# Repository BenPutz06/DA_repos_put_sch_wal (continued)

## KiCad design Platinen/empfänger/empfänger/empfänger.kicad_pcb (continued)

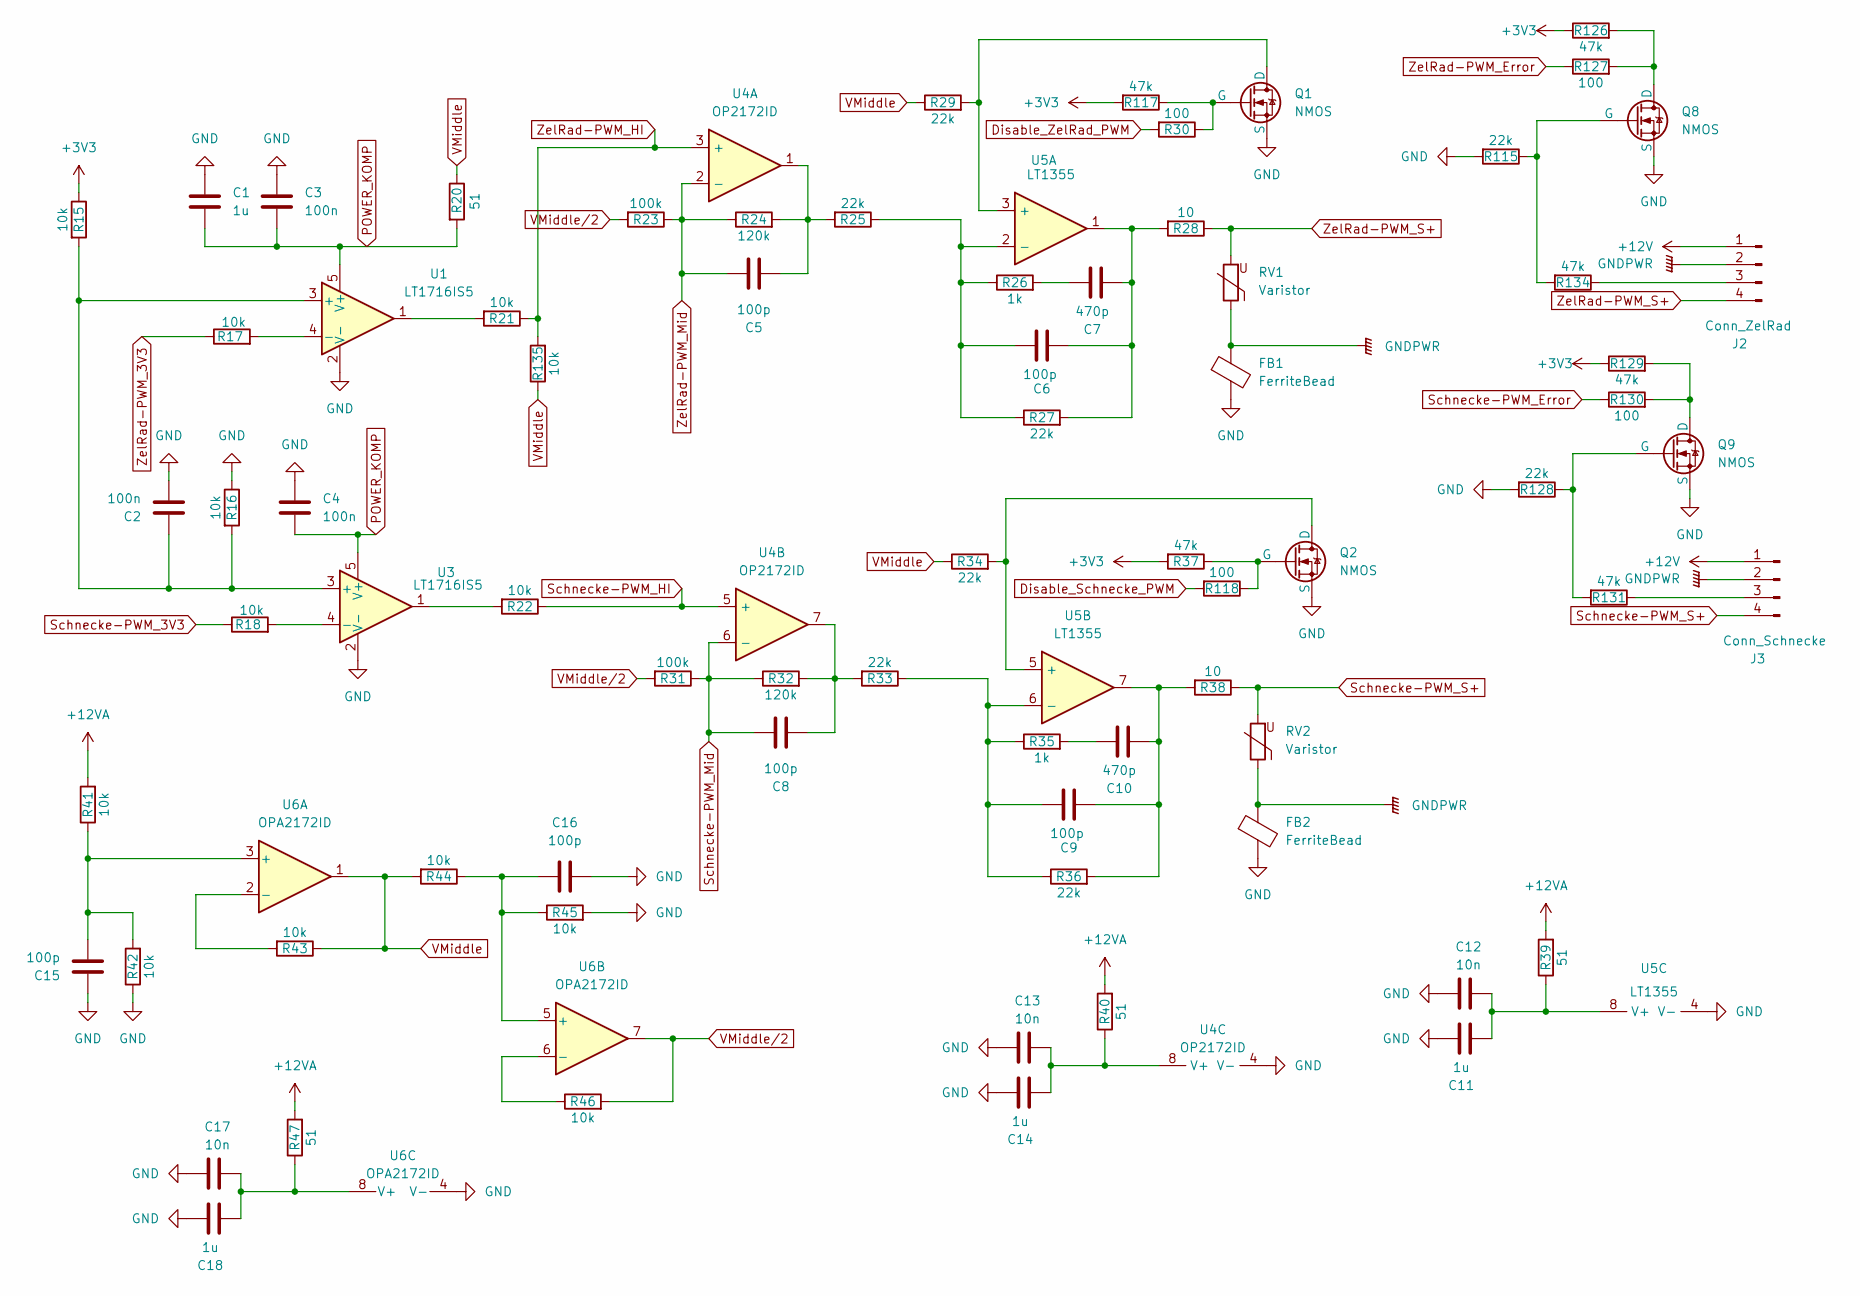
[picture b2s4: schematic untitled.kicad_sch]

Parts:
C1, C11, C14, C18: 1u; C_1206_3216Metric; Part-NO C1206C105K4RAC
C2, C3, C4: 100n; C_0805_2012Metric; Part-NO CC0805KRX7R9BB104
C5, C6, C8, C9, C15, C16: 100p; C_0805_2012Metric; Part-NO C0805C101J5GACTU
C7, C10: 470p; C_0805_2012Metric
C12, C13, C17: 10n; C_0603_1608Metric; Part-NO CC0603KRX7R9BB103
FB1, FB2: FerriteBead; R_1206_3216Metric; Part-NO WE-CBF_74279218
J2: Conn_ZelRad; PhoenixContact_MSTBVA_2,5_4-G-5,08_1x04_P5.08mm_Vertical; Part-NO MSTBV2_5/4-G-5_08
J3: Conn_Schnecke; PhoenixContact_MSTBVA_2,5_4-G-5,08_1x04_P5.08mm_Vertical; Part-NO MSTBV2_5/4-G-5_08
Q1, Q2, Q8, Q9: NMOS; TSOT-23; Part-NO FDV305N
R15, R16, R17, R18, R21, R22, R41, R42, R43, R44, R45, R46, R135: 10k; R_0603_1608Metric; Part-NO CRG0603F10K
R20, R39, R40, R47: 51; R_1206_3216Metric; Part-NO CRG1206F51R
R23, R31: 100k; R_0603_1608Metric; Part-NO CRG0603F100K
R24, R32: 120k; R_0603_1608Metric; Part-NO CRG0603F120K
R25, R27, R29, R33, R34, R36, R115, R128: 22k; R_0603_1608Metric; Part-NO CRG0603F22K
R26, R35: 1k; R_0603_1608Metric; Part-NO CRG0603F1K0
R28, R38: 10; R_1206_3216Metric
R30, R118, R127, R130: 100; R_0603_1608Metric
R37, R117, R126, R129: 47k; R_0603_1608Metric; Part-NO CRG0603F47K
R131, R134: 47k; R_0603_1608Metric; Part-NO CRG0603F22K
RV1, RV2: Varistor; R_1206_3216Metric; Part-NO WE-VS_82541110
U1, U3: LT1716IS5; SOT-23-5; Part-NO LT1716IS5
U4: OP2172ID; SOIC-8_3.9x4.9mm_P1.27mm; Part-NO OP2172ID
U5: LT1355; SOIC-8_3.9x4.9mm_P1.27mm; Part-NO LT1355CS8
U6: OPA2172ID; SOIC-8_3.9x4.9mm_P1.27mm; Part-NO OPA2172ID

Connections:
+3V3: R15.1, R37.2, R117.2, R126.1, R129.1; also elsewhere on the board
+12V: J2.1, J3.1; also elsewhere on the board
+12VA: R39.2, R40.2, R41.2, R47.2; also elsewhere on the board
Disable_Schnecke_PWM: R118.2; also elsewhere on the board
Disable_ZelRad_PWM: R30.2; also elsewhere on the board
GND: C1.1, C2.1, C3.1, C4.1, C11.2, C12.1, C13.1, C14.2, C15.1, C16.2, C17.1, C18.2, FB1.2, FB2.2, Q1.2 (S), Q2.2 (S), Q8.2 (S), Q9.2 (S), R16.1, R42.1, R45.2, R115.2, R128.2, U1.2 (V-), U3.2 (V-), U4.4 (V-), U5.4 (V-), U6.4 (V-); also elsewhere on the board
GNDPWR: FB1.1, FB2.1, J2.2, J3.2, RV1.1, RV2.1; also elsewhere on the board
unnamed: C5.1, R24.2, R25.2, U4.1
unnamed: C6.1, C7.1, R27.2, R28.2, U5.1
unnamed: C7.2, R26.2
unnamed: C8.1, R32.2, R33.2, U4.7
unnamed: C9.1, C10.1, R36.2, R38.2, U5.7
unnamed: C10.2, R35.2
unnamed: J2.3, R134.1
unnamed: J3.3, R131.1
unnamed: Q1.3 (D), R29.2, U5.3 (+)
unnamed: Q1.1 (G), R30.1, R117.1
unnamed: Q2.3 (D), R34.2, U5.5 (+)
unnamed: Q2.1 (G), R37.1, R118.1
unnamed: Q8.3 (D), R126.2, R127.2
unnamed: Q8.1 (G), R115.1, R134.2
unnamed: Q9.3 (D), R129.2, R130.2
unnamed: Q9.1 (G), R128.1, R131.2
unnamed: R21.2, U1.1
unnamed: R22.2, U3.1
unnamed: C2.2, R15.2, R16.2, U1.3 (+), U3.3 (+)
unnamed: R17.2, U1.4 (-)
unnamed: R18.2, U3.4 (-)
unnamed: C13.2, C14.1, R40.1, U4.8 (V+)
unnamed: C6.2, R25.1, R26.1, R27.1, U5.2 (-)
unnamed: C9.2, R33.1, R35.1, R36.1, U5.6 (-)
unnamed: C11.1, C12.2, R39.1, U5.8 (V+)
unnamed: C15.2, R41.1, R42.2, U6.3 (+)
unnamed: R43.2, U6.2 (-)
unnamed: C16.1, R44.1, R45.1, U6.5 (+)
unnamed: R46.1, U6.6 (-)
unnamed: C17.2, C18.1, R47.1, U6.8 (V+)
POWER_KOMP: C1.2, C3.2, C4.2, R20.2, U1.5 (V+), U3.5 (V+); also elsewhere on the board
Schnecke-PWM_3V3: R18.1; also elsewhere on the board
Schnecke-PWM_Error: R130.1; also elsewhere on the board
Schnecke-PWM_HI: R22.1, U4.5 (+)
Schnecke-PWM_Mid: C8.2, R31.1, R32.1, U4.6 (-); also elsewhere on the board
Schnecke-PWM_S+: J3.4, R38.1, RV2.2
VMiddle: R20.1, R29.1, R34.1, R43.1, R44.2, R135.1, U6.1; also elsewhere on the board
VMiddle/2: R23.2, R31.2, R46.2, U6.7
ZelRad-PWM_3V3: R17.1; also elsewhere on the board
ZelRad-PWM_Error: R127.1; also elsewhere on the board
ZelRad-PWM_HI: R21.1, R135.2, U4.3 (+)
ZelRad-PWM_Mid: C5.2, R23.1, R24.1, U4.2 (-); also elsewhere on the board
ZelRad-PWM_S+: J2.4, R28.1, RV1.2

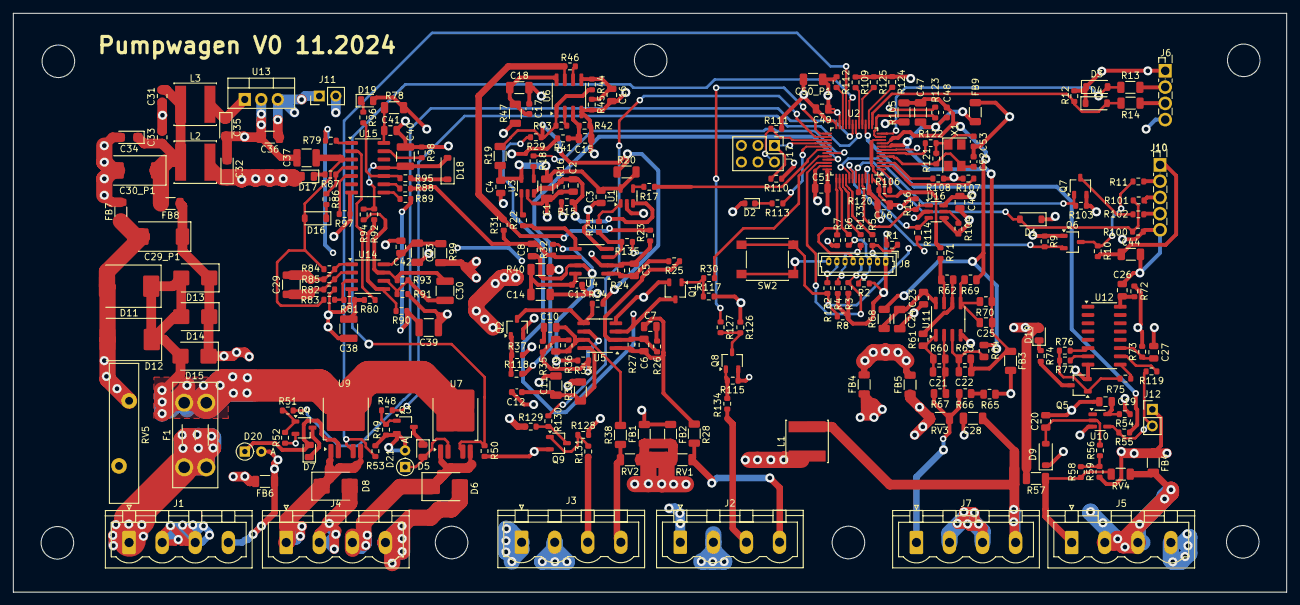
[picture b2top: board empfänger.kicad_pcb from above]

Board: 4 copper layers, 195.6 x 88.9 mm, 275 parts (0 on the bottom side), 160 nets.

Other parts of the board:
FB4#2: FerriteBead; R_1206_3216Metric
R19: 51; R_1206_3216Metric

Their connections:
GND: FB4#2.1; also elsewhere on the board
GNDPWR: FB4#2.2; also elsewhere on the board
POWER_KOMP: R19.2; also elsewhere on the board
VMiddle: R19.1; also elsewhere on the board

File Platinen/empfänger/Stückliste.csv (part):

'Reference';'Value';'Datasheet';'Footprint';'Qty';'DNP';'Beschreibung';'Part-NO'
'C1,C11,C14,C18,C24,C47';'1u';'~';'Capacitor_SMD:C_1206_3216Metric';'6';'';'Unpolarized capacitor';'C1206C105K4RAC'
'C2,C3,C4,C19,C22,C23,C25,C26,C27,C41,C42,C45,C46,C49,C51';'100n';'~';'Capacitor_SMD:C_0805_2012Metric';'15';'';'Unpolarized capacitor';'-- verschiedene Werte --'
'C5,C6,C8,C9,C15,C16,C20,C21';'100p';'~';'Capacitor_SMD:C_0805_2012Metric';'8';'';'Unpolarized capacitor';'C0805C101J5GACTU'
'C7,C10';'470p';'~';'Capacitor_SMD:C_0805_2012Metric';'2';'';'Unpolarized capacitor';''
'C12,C13,C17,C48';'10n';'~';'Capacitor_SMD:C_0603_1608Metric';'4';'';'Unpolarized capacitor';'CC0603KRX7R9BB103 '
'C28,C36,C43,C44,C50_P1';'10u';'~';'Capacitor_SMD:C_1206_3216Metric';'5';'';'-- verschiedene Werte --';'-- verschiedene Werte --'
'C29,C30';'10p';'~';'Capacitor_SMD:C_1210_3225Metric';'2';'';'Unpolarized capacitor';'12101C105KAZ2A '
'C29_P1,C30_P1';'47u';'~';'Capacitor_Tantalum_SMD:CP_EIA-7343-30_AVX-N';'2';'';'Polarized capacitor';'TPSE476K025R0080 '
'C31,C33';'100n_P';'~';'Capacitor_SMD:C_0805_2012Metric';'2';'';'Unpolarized capacitor';'CC0805KRX7R9BB104 '
'C32,C34,C35';'10u_P';'~';'Capacitor_Tantalum_SMD:CP_EIA-3216-18_Kemet-A';'3';'';'Unpolarized capacitor';''
'C37,C38,C39,C40';'1u_100V';'~';'Capacitor_SMD:C_1210_3225Metric';'4';'';'Unpolarized capacitor';'12101C105KAZ2A '
'C52,C53';'12p';'~';'Capacitor_SMD:C_0603_1608Metric';'2';'';'Unpolarized capacitor';'CC0603JRNPO9BN120 '
'D1,D3,D4,D9,D16,D18';'D_Schottky';'~';'Diode_SMD:D_SOD-123';'6';'';'Schottky diode';'MBR0530_30V_0A5'
'D2';'LED_uC';'~';'LED_SMD:LED_0603_1608Metric';'1';'';'Light emitting diode';'SML_512MW '
'D5,D7,D10,D17,D19';'LED';'-- verschiedene Werte --';'LED_SMD:LED_0805_2012Metric';'5';'';'-- verschiedene Werte --';'XZCDGK54W-1VF '
'D6,D8';'SMBJ26A';'~';'Diode_SMD:D_SMB';'2';'';'Schottky diode';'SMBJ26A '
'D11,D12';'SM15T27A';'https://www.vishay.com/docs/88748/ss22.pdf';'Diode_SMD:D_SMC';'2';'';'40V 2A Schottky Diode, SMA';'SM15T27A '
'D13,D14,D15';'SS24';'https://www.vishay.com/docs/88748/ss22.pdf';'Diode_SMD:D_SMB';'3';'';'40V 2A Schottky Diode, SMA';'SS24-M3 '
'D20,D21';'1N4148';'~';'Diode_THT:D_DO-35_SOD27_P2.54mm_Vertical_AnodeUp';'2';'';'Diode';'1N4148WS_ES_08 '
'F1';'15A';'~';'Fuse:Fuseholder_Blade_Mini_Keystone_3568';'1';'';'Fuse';'FUSE-HOLD_01530008Z '
'FB1,FB2,FB3,FB4,FB5,FB6,FB7,FB8,FB9';'FerriteBead';'~';'Resistor_SMD:R_1206_3216Metric';'9';'';'Ferrite bead';'WE-CBF_74279218 '
'J1';'Versorgung Traktor';'~';'Connector_Phoenix_MSTB:PhoenixContact_MSTBVA_2,5_4-G-5,08_1x04_P5.08mm_Vertical';'1';'';'Generic connector, single row, 01x04, script generated';'MSTBV2_5/4-G-5_08 '
'J2';'Conn_ZelRad';'~';'Connector_Phoenix_MSTB:PhoenixContact_MSTBVA_2,5_4-G-5,08_1x04_P5.08mm_Vertical';'1';'';'Generic connector, single row, 01x04, script generated';'MSTBV2_5/4-G-5_08 '
'J3';'Conn_Schnecke';'~';'Connector_Phoenix_MSTB:PhoenixContact_MSTBVA_2,5_4-G-5,08_1x04_P5.08mm_Vertical';'1';'';'Generic connector, single row, 01x04, script generated';'MSTBV2_5/4-G-5_08 '
'J4';'Conn_Schubwand';'~';'Connector_Phoenix_MSTB:PhoenixContact_MSTBVA_2,5_4-G-5,08_1x04_P5.08mm_Vertical';'1';'';'Generic connector, single row, 01x04, script generated';'MSTBV2_5/4-G-5_08 '
'J5';'Conn_ZelRadDrehzhl';'~';'Connector_Phoenix_MSTB:PhoenixContact_MSTBVA_2,5_4-G-5,08_1x04_P5.08mm_Vertical';'1';'';'Generic connector, single row, 01x04, script generated';'MSTBV2_5/4-G-5_08 '
'J6';'PC_Conn';'~';'Library:TerminalBlock_Phoenix_PTSM-0,5-4-2.5-V-THR_1x04_P2.50mm_Vertical';'1';'';'Generic connector, single row, 01x04, script generated';'MCV-0_5-4-G-2_5'
'J7';'Conn_PumpeDruck';'~';'Connector_Phoenix_MSTB:PhoenixContact_MSTBVA_2,5_4-G-5,08_1x04_P5.08mm_Vertical';'1';'';'Generic connector, single row, 01x04, script generated';'MSTBV2_5/4-G-5_08 '
'J8';'Programmer_Conn';'~';'Connector_Molex:Molex_PicoBlade_53047-0810_1x08_P1.25mm_Vertical';'1';'';'Generic connector, single row, 01x08, script generated';'53047-0810'
'J9,J13,J14,J15,J16,J18,J19';'Montageloch';'~';'MountingHole:MountingHole_5mm';'7';'';'Generic connector, single row, 01x01, script generated';''
'J10';'Conn_RFmodul';'~';'Library:TeminalBlock_Phoenix_5Pol';'1';'';'Generic connector, single row, 01x05, script generated';'MCV-0_5-5-G-2_5 '
'J11';'Conn_01x02_Socket';'~';'Connector_PinHeader_2.54mm:PinHeader_1x02_P2.54mm_Vertical';'1';'';'Generic connector, single row, 01x02, script generated';'JMP_1X2P_0901200122 '
'J12';'Conn_01x02_Pin';'~';'Connector_PinHeader_2.54mm:PinHeader_1x02_P2.54mm_Vertical';'1';'';'Generic connector, single row, 01x02, script generated';'JMP_1X2P_0901200122 '
'J17';'Conn_02x03_Counter_Clockwise';'~';'Connector_PinHeader_2.54mm:PinHeader_2x03_P2.54mm_Vertical';'1';'';'Generic connector, double row, 02x03, counter clockwise pin numbering scheme (similar to DIP package numbering), script generated (kicad-library-utils/schlib/autogen/connector/)';'TSW-102-07-T-T '
'L1,L3';'100u';'~';'Inductor_SMD:L_Sunlord_SWPA6045S';'2';'';'Inductor';'74404064101 '
'L2';'100u_P';'~';'Inductor_SMD:L_Sunlord_SWPA6045S';'1';'';'Inductor';''
'Q1,Q2,Q3,Q4,Q5,Q6,Q7,Q8,Q9';'NMOS';'https://ngspice.sourceforge.io/docs/ngspice-html-manual/manu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;'Package_TO_SOT_SMD:TSOT-23';'9';'';'N-MOSFET transistor, drain/source/gate';'FDV305N '
'R1,R2,R3,R4,R7,R37,R117,R126,R129,R131,R134';'47k';'~';'Resistor_SMD:R_0603_1608Metric';'11';'';'-- verschiedene Werte --';'-- verschiedene Werte --'
'R5,R6,R28,R38,R71';'10';'~';'-- verschiedene Werte --';'5';'';'-- verschiedene Werte --';''
'R8,R23,R31,R49,R52,R73,R100,R103,R104,R110,R111,R120';'100k';'~';'Resistor_SMD:R_0603_1608Metric';'12';'';'CRG0603F100K';'CRG0603F100K'
'R9,R15,R16,R17,R18,R21,R22,R41,R42,R43,R44,R45,R46,R79,R80,R86,R88,R89,R95,R97,R98,R101,R114,R116,R135';'10k';'~';'Resistor_SMD:R_0603_1608Metric';'25';'';'CRG0603F10K';'CRG0603F10K'
'R10,R56';'4k7';'~';'Resistor_SMD:R_0603_1608Metric';'2';'';'CRG0603F4K7';'CRG0603F4K7'
'R11,R13,R14,R30,R48,R51,R55,R65,R66,R102,R106,R118,R119,R127,R130';'100';'~';'-- verschiedene Werte --';'15';'';'-- verschiedene Werte --';''
'R12';'330k';'~';'Resistor_SMD:R_0603_1608Metric';'1';'';'CRG0603F100R';'CRG0603F100R'
'R20,R39,R40,R47,R68,R78,R99,R105';'51';'~';'Resistor_SMD:R_1206_3216Metric';'8';'';'CRG1206F51R';'CRG1206F51R'
'R24,R32';'120k';'~';'Resistor_SMD:R_0603_1608Metric';'2';'';'CRG0603F120K';'CRG0603F120K'
'R25,R27,R29,R33,R34,R36,R75,R76,R77,R115,R128';'22k';'~';'Resistor_SMD:R_0603_1608Metric';'11';'';'CRG0603F22K';'CRG0603F22K'
'R26,R35';'1k';'~';'Resistor_SMD:R_0603_1608Metric';'2';'';'CRG0603F1K0';'CRG0603F1K0'
'R50,R53,R113';'620';'~';'Resistor_SMD:R_0603_1608Metric';'3';'';'CRG0603F620R';'CRG0603F620R'
'R54,R72,R132,R133';'0';'~';'Resistor_SMD:R_0603_1608Metric';'4';'';'CRG0603ZR';'CRG0603ZR'
'R57';'12k';'~';'Resistor_SMD:R_1206_3216Metric';'1';'';'CRG1206F12K';'CRG1206F12K'
'R58';'150k';'~';'Resistor_SMD:R_0603_1608Metric';'1';'';'CRG0603F150K';'CRG0603F150K'
'R59';'62k';'~';'Resistor_SMD:R_0603_1608Metric';'1';'';'CRG0603F62K';'CRG0603F62K'
'R60,R61,R62,R69,R70';'115k';'~';'Resistor_SMD:R_0805_2012Metric';'5';'';'RR1220Q-1153-D-M';'RR1220Q-1153-D-M'
'R63';'12k4';'~';'Resistor_SMD:R_0805_2012Metric';'1';'';'RR1220Q-1242-D-M';'RR1220Q-1242-D-M'
'R64';'8k25';'~';'Resistor_SMD:R_0805_2012Metric';'1';'';'RR1220Q-8251-D-M';'RR1220Q-8251-D-M'
'R67';'121k';'~';'Resistor_SMD:R_0805_2012Metric';'1';'';'RR1220Q-1213-D-M';'RR1220Q-1213-D-M'
'R74,R87,R96';'3k3';'~';'Resistor_SMD:R_0603_1608Metric';'3';'';'CRG0603F3K3';'CRG0603F3K3'
'R81,R82,R85,R90,R91,R93';'220k';'~';'Resistor_SMD:R_0603_1608Metric';'6';'';'CRG0603F220K';'CRG0603F220K'
'R83,R92';'20k';'~';'Resistor_SMD:R_0603_1608Metric';'2';'';'CRG0603F20K';'CRG0603F20K'
'R84,R94';'200k';'~';'Resistor_SMD:R_0603_1608Metric';'2';'';'CRG0603F200K';'CRG0603F200K'
'R107,R108,R109,R112,R121,R123,R124,R125';'1M';'~';'Resistor_SMD:R_0603_1608Metric';'8';'';'CRG0603F1M0';'CRG0603F1M0'
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
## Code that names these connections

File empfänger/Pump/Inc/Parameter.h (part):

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	 #if (USE_NUCLEO == 2)

	//USART2 GPIO Configuration
  //PB10   ------> USART2_TX
  //PB11  ------> USART2_RX
	
	#define 	UART_PC											USART3
	#define 	UART_PC_Baudrate						19200
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 
 
 //USART2 GPIO Configuration
  //PA2   ------> USART2_TX
  //PA3   ------> USART2_RX
	
	#define 	UART_PC											USART2
	#define 	UART_PC_Baudrate						19200
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
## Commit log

2025-03-20 .gitattributes und .gitignore hinzufügen.
2025-03-20 Projektdateien hinzufügen.
2025-03-20 Stand 20.03.2025
